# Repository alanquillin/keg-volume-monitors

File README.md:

# DIY Keg Volume Monitors

While there are many commercially available monitors for kegs out there, this project is designed for the DIY/tinkerer at heart and aimed to be a more cost effective way to add volume monitors to your kegs.  The core of these monitors is the particle.io Photon 2 micro-controller.  This low cost micro-controller adds Wifi and BluetoothLE support as well and integrated cloud.  This allows the keg monitor service to get stats and execute functions against the devices even when they are not on the same network. The particle.io cloud is free (for up to 100 devices) so it makes it perfect for this type of DIY project.  While there are cheaper micro-controllers out there, the Photon 2 was chosen because its extra features were worth the extra few dollars.

## Monitors

- [Weight Scale](./monitors/weight/README.md): Monitors the volume of the keg based on the current weight.
- Flow Monitor _(coming soon)_: Monitors the remaining volume in the keg bacged on how much liquid flowed through the sensors.

## The web service

The core of all of this is the web service.  This offers an API, both for the devices to post too, as well as external services to integrate with.  There is also a light weight UI for viewing the status of and managing the devices.  The service also proxies the calls to particle cloud to execute certain functions on the different devices.

## Whats next?

See our [issues page](https://github.com/alanquillin/keg-volume-monitors/issues) for upcoming milestones and changes on our roadmap.

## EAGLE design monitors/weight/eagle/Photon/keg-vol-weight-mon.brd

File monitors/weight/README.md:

# Weight Based Keg Volume Monitor

Inspired by the now discontinued Plaato keg, this monitor uses the weight of the keg over time to determine the current
 volume based on the weight of the empty keg and the weight of a full keg.  I love the Plaato keg, and was sad when they
 announced their pivot away from home brewing gear and would no longer be selling, innovating or supporting the Plaato
 keg.  In my search I found a few other DIY clones using low cost hardware and existing technologies.  However, I wanted
 to build some truly DIY with fully opensource software.  So I designed my own keg scale using the Particle Photon 2 platform.

## Parts required

- [Particle Photon2](https://store.particle.io/products/photon-2) (optionally will work with discontinued Photon or Argon)
- [4 Load Cells w/ HX711 amplifier](https://www.amazon.com/Bridge-Digital-Amplifier-Arduino-DIYmalls/dp/B086ZHXNJH)
- [5mm RGB Led (common cathode)](https://www.amazon.com/PATIKIL-Emitting-Mounting-Bracket-Transparent/)
- 3X 330 ohm Resistor
- [5mm LED holder](https://www.amazon.com/PATIKIL-Emitting-Mounting-Bracket-Transparent/dp/B0C54Y99NQ)

### Optional components

- Micro USB cable (is using the optinal riser boards below, I would recommend a cable with extremely slim connectors
like [these](https://www.amazon.com/dp/B09XKYP32W).  The .stl files for the case add additional room for the cables, but its better to be safe than sorry ;P)
- [6mmX6mm single pole push button switch](https://www.amazon.com/dp/B07WF76VHT)
- 10k Ohm resistor

#### Optional Parts for custom riser boards

I have added the [EAGLE files](./eagle) to manufacture helper riser boards simplify and cleanup the internal wiring.  Please [contact me](mailto:alanquillin@gmail.com) for more information. 

- JST-PH connectors
  - 4 pole connectors
    - 3 X [S4B-PH-K-S](https://www.digikey.com/en/products/detail/jst-sales-america-inc/S4B-PH-K-S/926628) right angle female through hole solder connectors
    - 1 X [B4B-PH-K-S](https://www.digikey.com/en/products/detail/jst-sales-america-inc/B4B-PH-K-S/926613) straight female through hole solder connector
    - 8 X [PHR-4](https://www.digikey.com/en/products/detail/jst-sales-america-inc/PHR-4/608606) male connectors
  - 3 pole
    - 4 X [S3B-PH-K-S](https://www.digikey.com/en/products/detail/jst-sales-america-inc/S3B-PH-K-S/926627) female through hole solder connectors
    - 8 X [PHR-3](https://www.digikey.com/en/products/detail/jst-sales-america-inc/PHR-3/527357) male connectors
  - 2 pole
    - 2 X [S2B-PH-K-S](https://www.digikey.com/en/products/detail/jst-sales-america-inc/S2B-PH-K-S/926626) female through hole solder connectors
    - 4 X [PHR-2](https://www.digikey.com/en/products/detail/jst-sales-america-inc/PHR-2/608607) male connectors
  - 20 X [SPH-004](https://www.digikey.com/en/products/detail/jst-sales-america-inc/SPH-004T-P0-5S/608759) crimp terminal pins
- [2m X 6MM self taping screws](https://www.amazon.com/dp/B01KXS7TOI).  The STLs do not have pre-drilled holed for the screws to hold the circuit boards, and thats because the risers are not perfect ;P, so self taping screws will allow you to screw right into the solid plastic.

## Links

- [Another DIY Plaato Keg clone](https://www.youtube.com/watch?v=QF1B8yD9jy4) from the [Trouble Brewing](https://www.youtube.com/@TroubleBrewing)
YouTube channel.  This one uses a NodeMCU 8266 module and Home Assistant Server.  However, I am not a huge fan of these modules or Home Assistant
and I wanted to build something with fully opensource software.
- [Wiring up and calibrating HX711 with 4 load cell using arduino](https://www.youtube.com/watch?v=LIuf2egMioA)

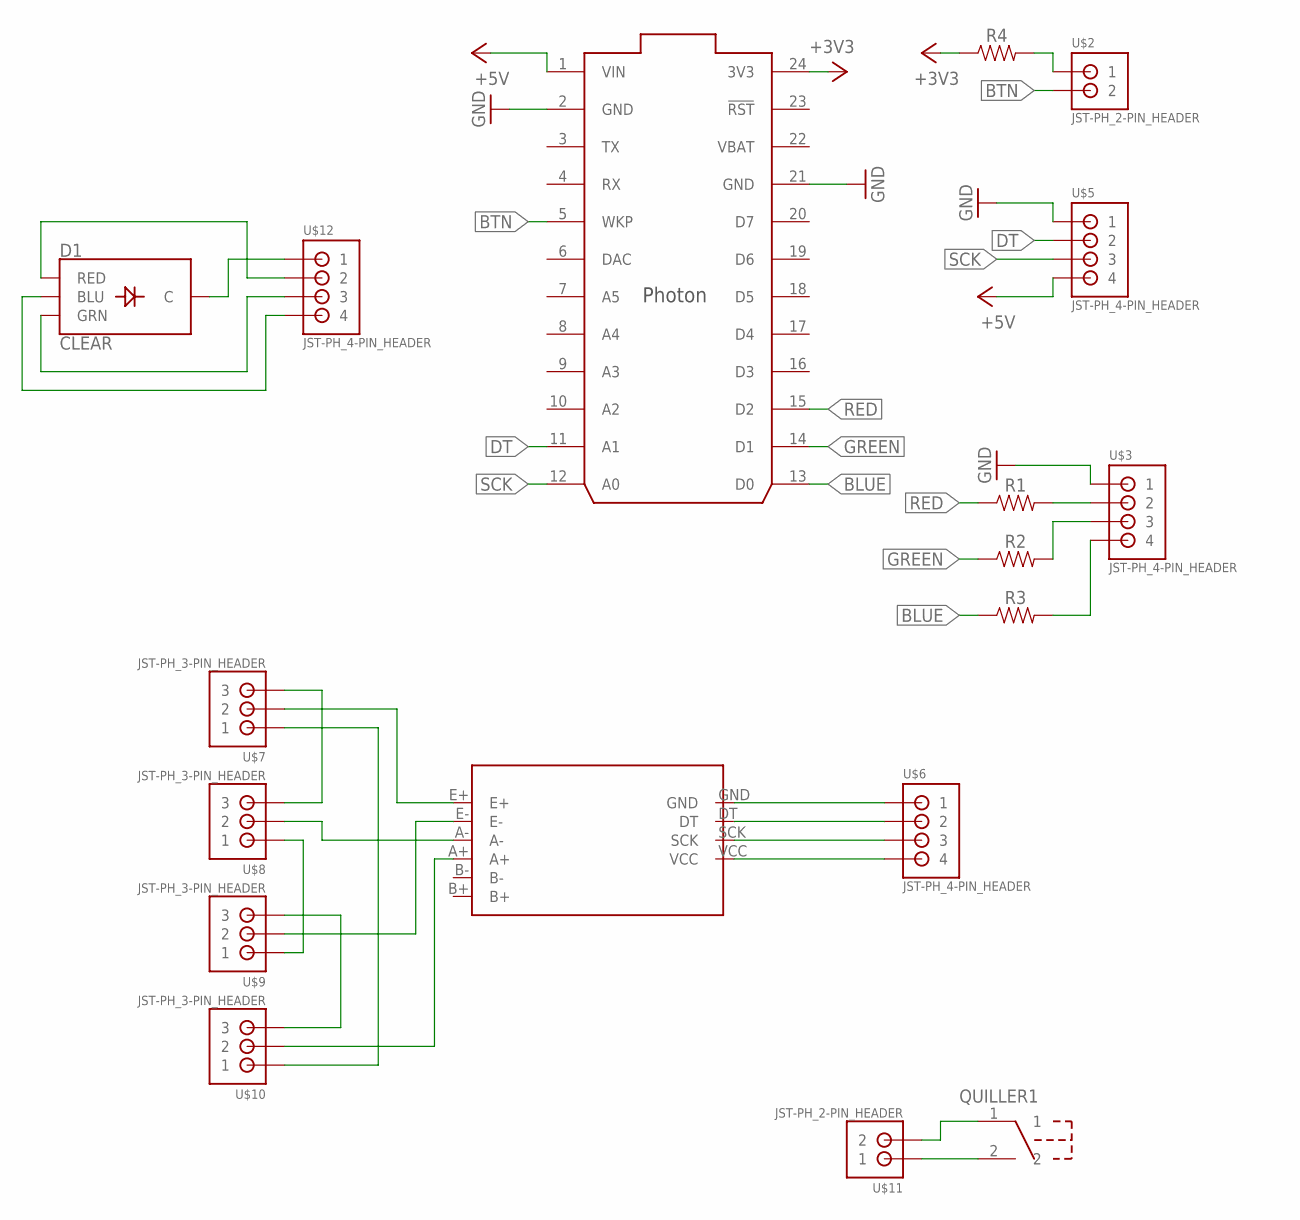
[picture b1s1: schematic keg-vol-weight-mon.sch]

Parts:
D1: CLEAR; LED-RGB-THRU
QUILLER1: 6MM-2PIN-TAC-MOM-SWITCH
R1, R2, R3, R4: AXIAL-0.3
U$1: PHOTON_WITH_HEADERS; PHOTON
U$2, U$11: JST-PH_2-PIN_HEADER; JST_B2B-PH_HEADER
U$3, U$5, U$6, U$12: JST-PH_4-PIN_HEADER; JST_B4B-PH_HEADER
U$4: HX711
U$7, U$8, U$9, U$10: JST-PH_3-PIN_HEADER; JST_B3B-PH_HEADER

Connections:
+3V3: R4.P$1 (1), U$1.24 (3V3)
+5V: U$1.1 (VIN), U$5.P4 (4)
BLUE: R3.P$1 (1), U$1.13 (D0)
BTN: U$1.5 (WKP), U$2.P2 (2)
DT: U$1.11 (A1), U$5.P2 (2)
GND: U$1.2 (GND), U$1.21 (GND), U$3.P1 (1), U$5.P1 (1)
GREEN: R2.P$1 (1), U$1.14 (D1)
unnamed: R2.P$2 (2), U$3.P3 (3)
unnamed: R3.P$2 (2), U$3.P4 (4)
unnamed: R4.P$2 (2), U$2.P1 (1)
unnamed: U$4.E+, U$7.P2 (2)
unnamed: R1.P$2 (2), U$3.P2 (2)
unnamed: U$4.A-, U$8.P2 (2)
unnamed: U$4.E-, U$9.P2 (2)
unnamed: U$4.A+, U$10.P2 (2)
unnamed: U$7.P3 (3), U$8.P3 (3)
unnamed: U$8.P1 (1), U$9.P1 (1)
unnamed: U$9.P3 (3), U$10.P3 (3)
unnamed: U$7.P1 (1), U$10.P1 (1)
unnamed: U$4.GND, U$6.P1 (1)
unnamed: U$4.DT, U$6.P2 (2)
unnamed: U$4.SCK, U$6.P3 (3)
unnamed: U$4.VCC, U$6.P4 (4)
unnamed: QUILLER1.1, U$11.P2 (2)
unnamed: QUILLER1.2, U$11.P1 (1)
unnamed: D1.2 (C), U$12.P1 (1)
unnamed: D1.4 (BLU), U$12.P4 (4)
unnamed: D1.3 (GRN), U$12.P3 (3)
unnamed: D1.1 (RED), U$12.P2 (2)
RED: R1.P$1 (1), U$1.15 (D2)
SCK: U$1.12 (A0), U$5.P3 (3)
VBAT: U$1.22 (VBAT)

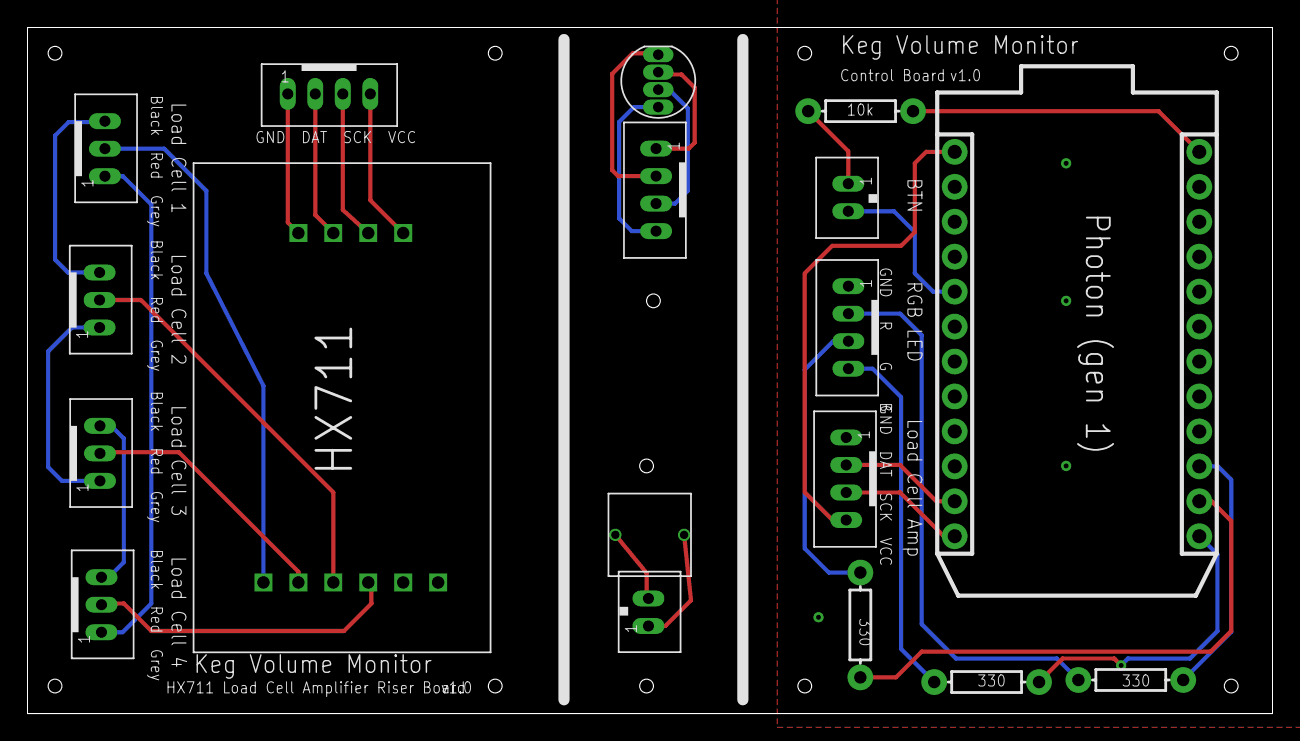
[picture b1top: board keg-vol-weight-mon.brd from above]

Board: 2 copper layers, 90.5 x 49.9 mm, 18 parts (0 on the bottom side), 31 nets.

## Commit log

2025-04-03 initial commit with wieght sensor
2025-04-04 Updated REDMEs
2025-04-04 added initial shell for the server
2025-04-07 added basic Device and Measurements CRUD API
2025-04-07 moved the RGBLED to shared library
2025-04-08 added the find device api method
2025-04-08 updated the save measurement api to simplify the data model
2025-04-08 Added the data service shared library
2025-04-14 Got the device registration process working
2025-04-19 more updates
2025-04-19 minor tweaks
2025-04-22 Changed to node 22 for angular 19 support
2025-04-22 updated data model for values for calculations
2025-04-22 Updated API for devices to include the volume calculations
2025-04-22 Added new angular UI with a simple page displaying device information
2025-05-02 Fixed device API resources and added volume unit conversions
2025-05-02 Added UI support for editing weight based device
2025-05-02 doc updates
2025-05-28 lots of stuff
2025-05-29 Updated UI with support for calibrating device
2025-05-29 Initial commit (#1)
    * initial commit with wieght sensor
    * Updated REDMEs
    * added initial shell for the server
    * added basic Device and Measurements CRUD API
    * moved the RGBLED to shared library
    * added the find device api method
2025-05-29 removed uncessary call to updated poetry depends when doing docker builds
2025-05-30 Cleanup and moved the test psql to run on non-standard 5433 port
2025-05-30 Fixed device creation
2025-05-31 fixed error where last measurements where always none
2025-06-11 Added auth
2025-06-11 added support for service accounts
2025-07-01 fixed auth issues and added edit profile page
2025-07-02 Added Users page
2025-07-03 more fixes
2025-07-03 Add auth to API/Web service (#2)
    * Added auth
    * added support for service accounts
    * fixed auth issues and added edit profile page
    * Added Users page
    * more fixes
2025-07-07 Fixed error with device sending beaer token
2025-07-07 added env.h file
2025-07-07 fixed env.h build errors
2025-07-07 added api key to devices list for admins
2025-07-08 added chip details to device list for admins
2025-07-08 fixed error when device is trying to update their status
2025-07-08 fixed auth check
2025-07-08 Added emptyKegWeightGrams to device API output
2025-07-08 added support for setting the empty keg weight on device
2025-07-17 fixed 308 error in prod
2025-07-17 version and app name fixes
2025-07-17 updates system dependency versions
2025-07-17 upgraded angular cli
2025-07-17 updated angular
2025-07-17 updated angular material
2025-07-17 updated to nedejs 24
2025-07-17 updated angular dependencies
2025-07-17 fix prod build error
2025-08-14 some naming issues

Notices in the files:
parts and their libraries:
SparkFun-LED: Licensing: Creative Commons ShareAlike 4.0 International - https://creativecommons.org/licenses/by-sa/4.0
Particle-Devices: Licensing: Designed by Particle.
